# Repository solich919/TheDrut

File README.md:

# The Drut
The Drut is a small project, in which I replicate the PCB design of "The Wire (SE-SE)" project from pictures:
> https://www.diyaudio.com/community/threads/the-wire-ultra-high-performance-headphone-amplifier-pcbs.179298/

The design was reproduced with manual assembly in mind (vias in pads), and I fit it on 2 layer PCB. It is a simple design for sure, but still a good learning experience.
The assembled amp works and sounds really good, but I have no way of measuring its performance.

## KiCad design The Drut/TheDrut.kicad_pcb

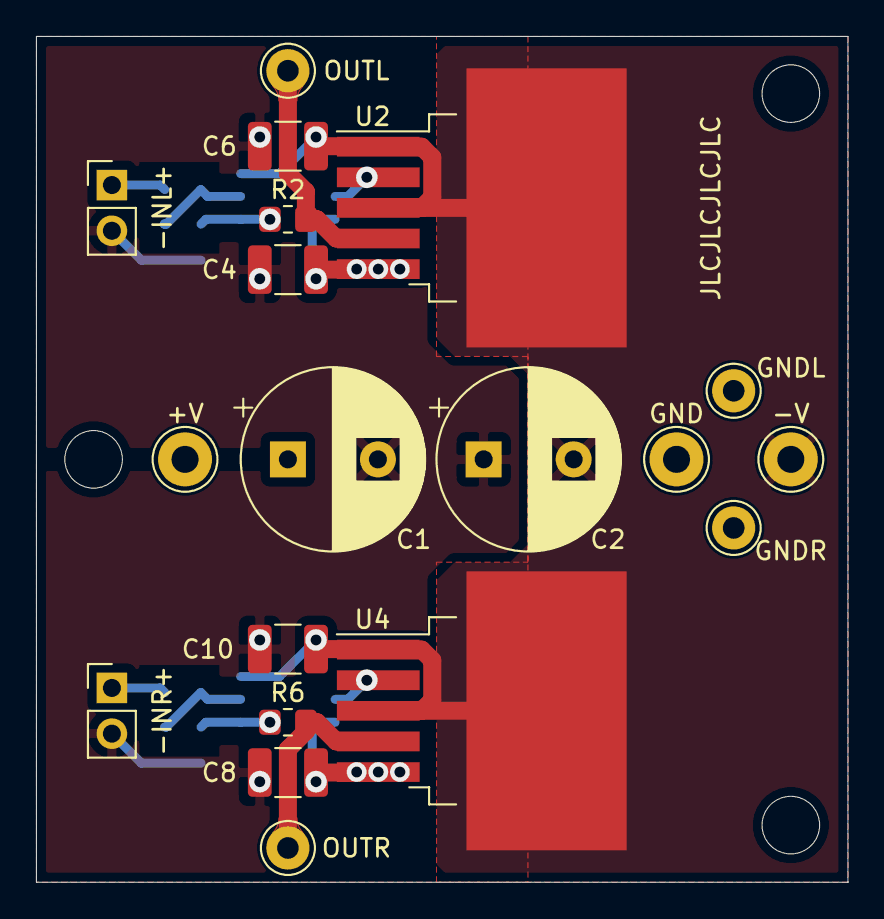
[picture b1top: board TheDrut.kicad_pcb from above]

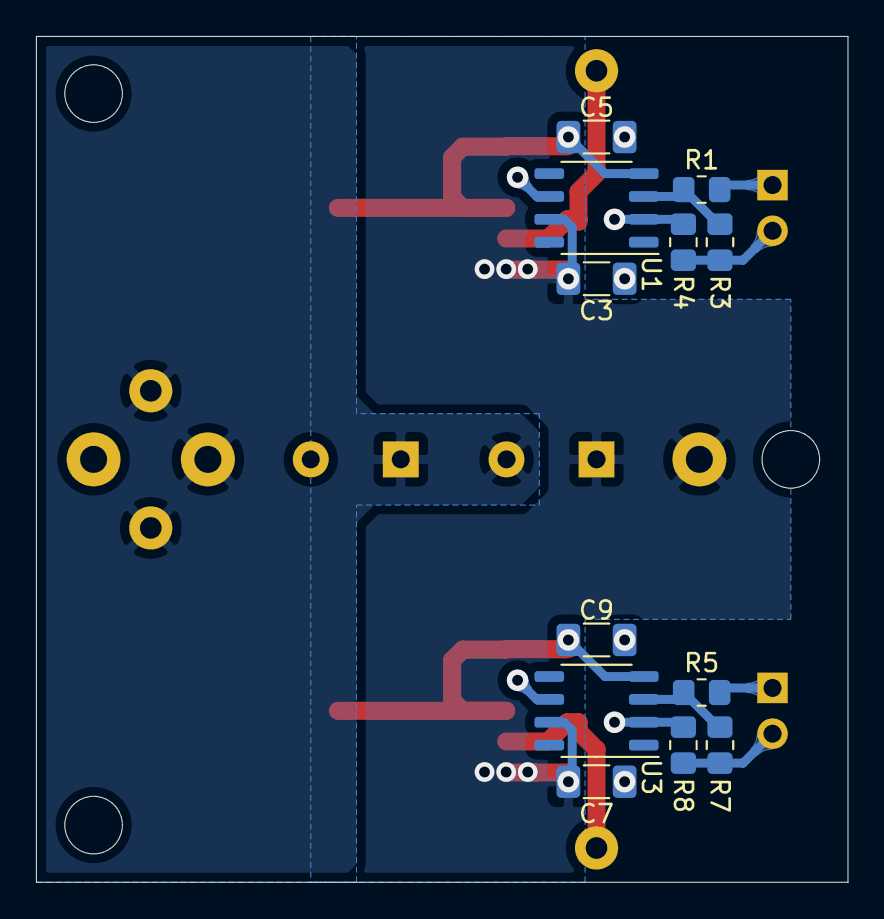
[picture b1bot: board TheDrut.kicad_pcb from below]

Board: 2 copper layers, 45.1 x 47.0 mm, 34 parts (12 on the bottom side), 13 nets.

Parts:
+V: Conn_01x01_Female; Pin_D1.3mm_L11.0mm_LooseFit
-INL+: In; PinHeader_1x02_P2.54mm_Vertical
-INR+: In; PinHeader_1x02_P2.54mm_Vertical
-V: Conn_01x01_Female; Pin_D1.3mm_L11.0mm_LooseFit
C1, C2: 470u; CP_Radial_D10.0mm_P5.00mm
C3, C5, C7, C9: 1u; C_1206_3216Metric_Pad1.33x1.80mm_HandSolder
C4, C6, C8, C10: 10u; C_1210_3225Metric_Pad1.33x2.70mm_HandSolder
GND: Conn_01x01_Female; Pin_D1.3mm_L11.0mm_LooseFit
GNDL: Out; Pin_D1.0mm_L10.0mm_LooseFit
GNDR: Out; Pin_D1.0mm_L10.0mm_LooseFit
H1, H2, H3: MountingHole; MountingHole_3.2mm_M3_ISO14580
OUTL: Out; Pin_D1.0mm_L10.0mm_LooseFit
OUTR: Out; Pin_D1.0mm_L10.0mm_LooseFit
R1, R2, R5, R6: 1k; R_0805_2012Metric_Pad1.20x1.40mm_HandSolder
R3, R4, R7, R8: 10k; R_0805_2012Metric_Pad1.20x1.40mm_HandSolder
U1, U3: OPA1641; SOP-8_3.9x4.9mm_P1.27mm
U2, U4: LME49600; TO-263-5_TabPin3_AAVID_7106

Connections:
+15V: +V.1, C1.1, C3.2, C4.1, C7.2, C8.1, U1.7, U2.5, U3.7, U4.5
-15V: -V.1, C2.2, C5.2, C6.2, C9.2, C10.2, U1.4, U2.1, U2.3, U3.4, U4.1, U4.3
GND: -INL+.2, -INR+.2, C1.2, C2.1, C3.1, C4.2, C5.1, C6.1, C7.1, C8.2, C9.1, C10.1, GND.1, GNDL.1, GNDR.1, R3.1, R4.1, R7.1, R8.1
unnamed: -INL+.1, R1.2
unnamed: OUTL.1, R2.2, U2.4
unnamed: -INR+.1, R5.2
unnamed: OUTR.1, R6.2, U4.4
unnamed: R1.1, R3.2, U1.3
unnamed: R2.1, R4.2, U1.2
unnamed: R5.1, R7.2, U3.3
unnamed: R6.1, R8.2, U3.2
unnamed: U1.6, U2.2
unnamed: U3.6, U4.2
